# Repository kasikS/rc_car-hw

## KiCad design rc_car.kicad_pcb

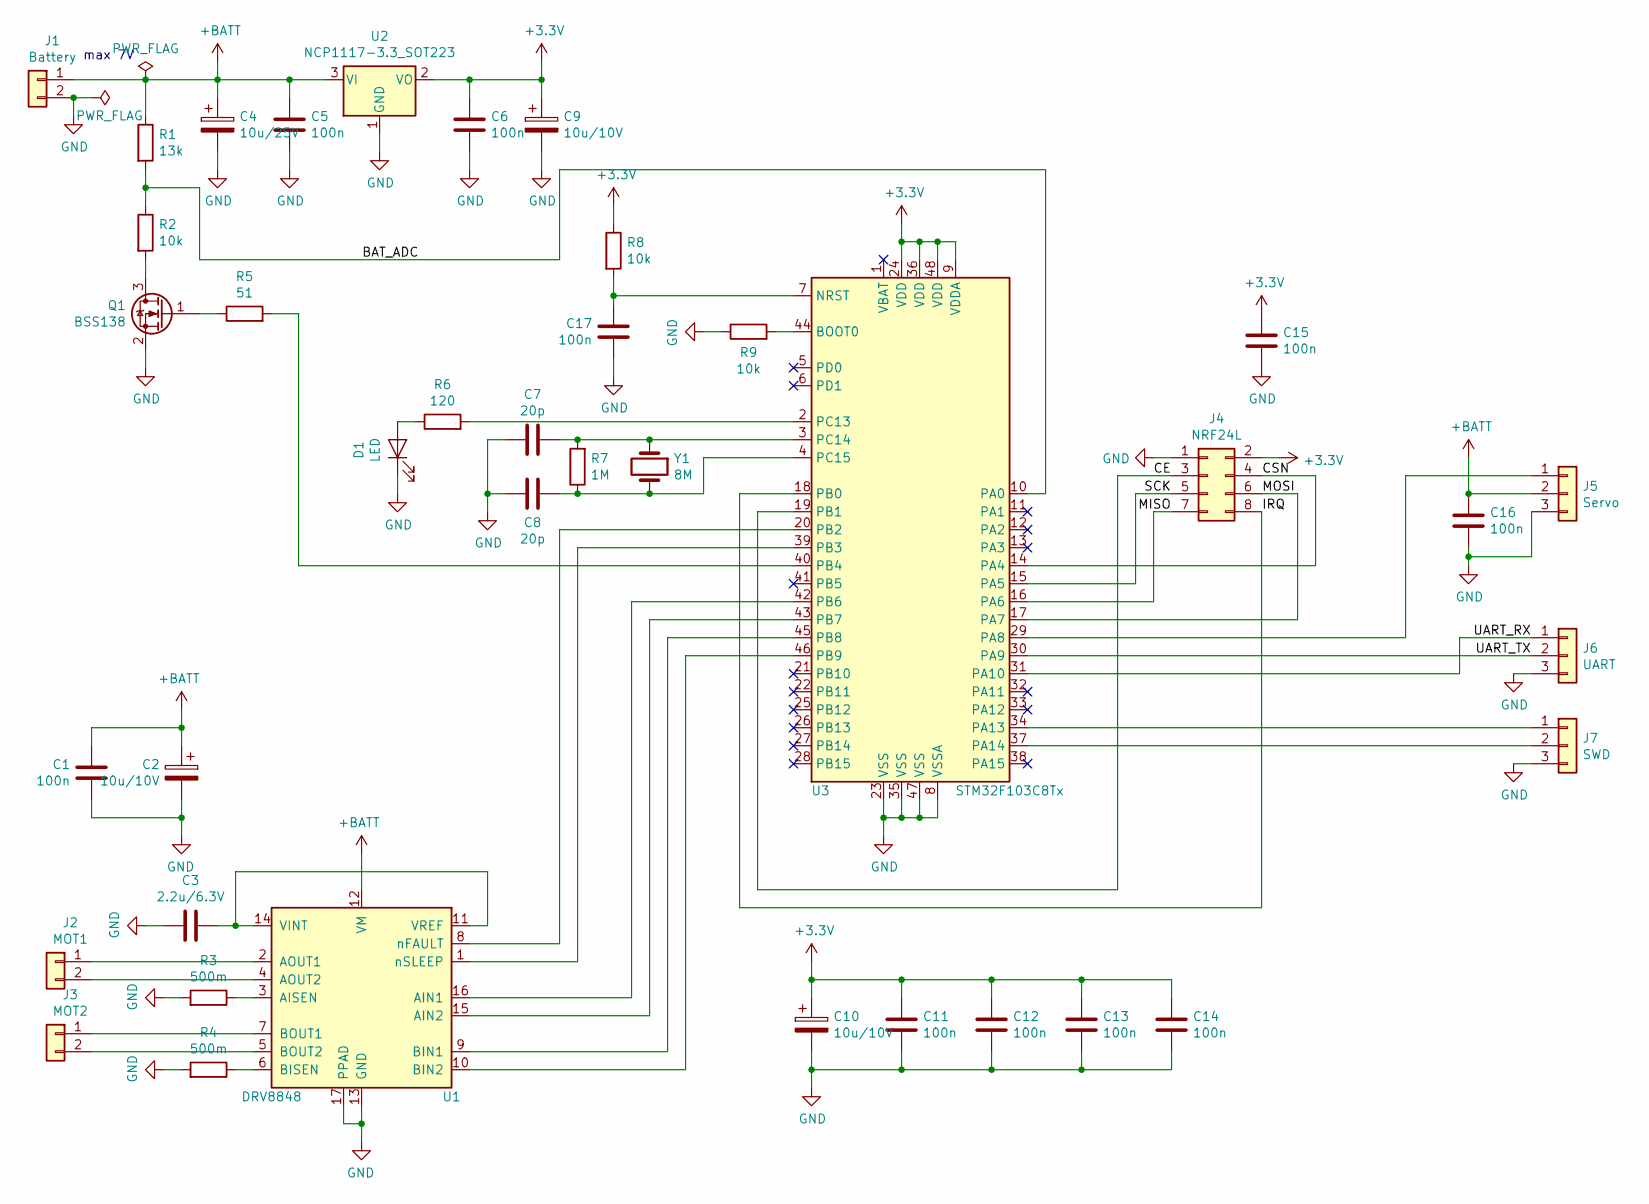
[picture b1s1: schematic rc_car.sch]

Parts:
C1: 100n; C_0805_2012Metric
C2, C9, C10: 10u/10V; C_0805_2012Metric
C3: 2.2u/6.3V; C_0805_2012Metric
C4: 10u/25V; C_0805_2012Metric
C5, C6, C11, C12, C13, C14, C15, C16, C17: 100n; C_0603_1608Metric
C7, C8: 20p; C_0603_1608Metric
D1: LED; D_0805_2012Metric
J1: Battery; PinHeader_1x02_P2.54mm_Vertical
J2: MOT1; PinHeader_1x02_P2.54mm_Vertical
J3: MOT2; PinHeader_1x02_P2.54mm_Vertical
J4: NRF24L; PinHeader_2x04_P2.54mm_Vertical
J5: Servo; PinHeader_1x03_P2.54mm_Vertical
J6: UART; PinHeader_1x03_P2.54mm_Vertical
J7: SWD; PinHeader_1x03_P2.54mm_Vertical
Q1: BSS138; SOT-23
R1: 13k; R_0603_1608Metric
R2, R8, R9: 10k; R_0603_1608Metric
R3, R4: 500m; R_0603_1608Metric
R5: 51; R_0603_1608Metric
R6: 120; R_0603_1608Metric
R7: 1M; R_0603_1608Metric
U1: DRV8848; TSSOP-16-1EP_4.4x5mm_P0.65mm
U2: NCP1117-3.3_SOT223; SOT-223-3_TabPin2
U3: STM32F103C8Tx; LQFP-48_7x7mm_P0.5mm
Y1: 8M; Crystal_SMD_HC49-SD

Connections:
+3V3: C6.1, C9.1, C10.1, C11.1, C12.1, C13.1, C14.1, C15.1, J4.2, R8.1, U2.2 (VO), U3.9 (VDDA), U3.24 (VDD), U3.36 (VDD), U3.48 (VDD)
+BATT: C1.1, C2.1, C4.1, C5.1, C16.1, J1.1, J5.2, R1.1, U1.12 (VM), U2.3 (VI)
/BAT_ADC: R1.2, R2.1, U3.10 (PA0)
/CE: J4.3, U3.19 (PB1)
/CSN: J4.4, U3.14 (PA4)
/IRQ: J4.8, U3.18 (PB0)
/MISO: J4.7, U3.16 (PA6)
/MOSI: J4.6, U3.17 (PA7)
/SCK: J4.5, U3.15 (PA5)
/UART_RX: J6.1, U3.31 (PA10)
/UART_TX: J6.2, U3.30 (PA9)
GND: C1.2, C2.2, C3.2, C4.2, C5.2, C6.2, C7.2, C8.2, C9.2, C10.2, C11.2, C12.2, C13.2, C14.2, C15.2, C16.2, C17.2, D1.1 (K), J1.2, J4.1, J5.3, J6.3, J7.3, Q1.2 (S), R3.2, R4.2, R9.1, U1.13 (GND), U1.17 (PPAD), U2.1 (GND), U3.8 (VSSA), U3.23 (VSS), U3.35 (VSS), U3.47 (VSS)
unnamed: C3.1, U1.11 (VREF), U1.14 (VINT)
unnamed: C7.1, R7.2, U3.3 (PC14), Y1.1
unnamed: C8.1, R7.1, U3.4 (PC15), Y1.2
unnamed: C17.1, R8.2, U3.7 (NRST)
unnamed: D1.2 (A), R6.1
unnamed: J2.1, U1.2 (AOUT1)
unnamed: J2.2, U1.4 (AOUT2)
unnamed: J3.1, U1.7 (BOUT1)
unnamed: J3.2, U1.5 (BOUT2)
unnamed: J5.1, U3.29 (PA8)
unnamed: J7.1, U3.34 (PA13)
unnamed: J7.2, U3.37 (PA14)
unnamed: Q1.1 (G), R5.1
unnamed: Q1.3 (D), R2.2
unnamed: R3.1, U1.3 (AISEN)
unnamed: R4.1, U1.6 (BISEN)
unnamed: R5.2, U3.40 (PB4)
unnamed: R6.2, U3.2 (PC13)
unnamed: R9.2, U3.44 (BOOT0)
unnamed: U1.1 (nSLEEP), U3.39 (PB3)
unnamed: U1.8 (nFAULT), U3.20 (PB2)
unnamed: U1.9 (BIN1), U3.45 (PB8)
unnamed: U1.10 (BIN2), U3.46 (PB9)
unnamed: U1.15 (AIN2), U3.43 (PB7)
unnamed: U1.16 (AIN1), U3.42 (PB6)

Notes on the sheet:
max 7V

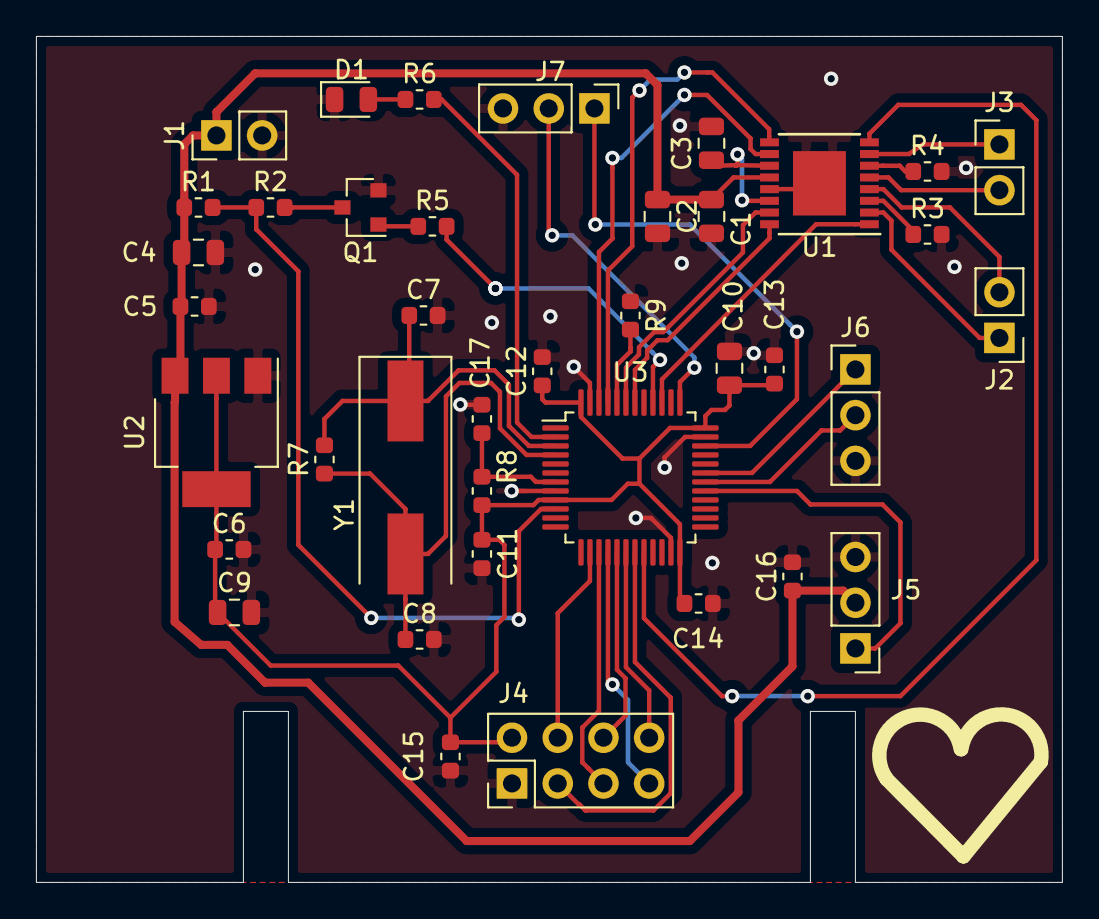
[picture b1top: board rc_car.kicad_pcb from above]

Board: 2 copper layers, 57.0 x 47.0 mm, 39 parts (0 on the bottom side), 37 nets.
